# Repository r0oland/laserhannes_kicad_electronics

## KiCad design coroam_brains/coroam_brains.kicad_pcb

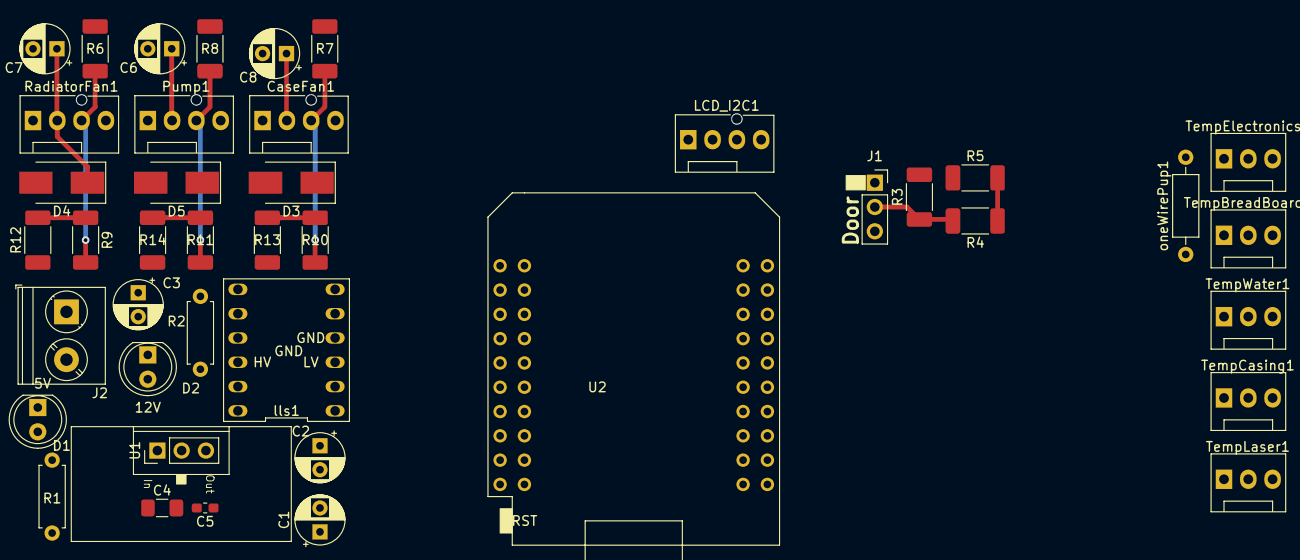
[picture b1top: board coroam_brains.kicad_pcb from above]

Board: 2 copper layers, 42 parts (0 on the bottom side), 23 nets.

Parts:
C1, C2, C3, C6, C7, C8: 22u; CP_Radial_D5.0mm_P2.50mm
C4: 0.33u; C_1206_3216Metric_Pad1.42x1.75mm_HandSolder
C5: 0.1u; C_0603_1608Metric_Pad1.05x0.95mm_HandSolder
CaseFan1: Fan_4pin; FanPinHeader_1x04_P2.54mm_Vertical
D1: 5V; LED_D5.0mm
D2: 12V; LED_D5.0mm
D3, D4, D5: D_Small_ALT; D_SMB_Handsoldering
J1: OpenCirc; PinSocket_1x03_P2.54mm_Vertical
J2: 12V_in; TerminalBlock_Phoenix_PT-1,5-2-5.0-H_1x02_P5.00mm_Horizontal
LCD_I2C1: LCD_I2C; FanPinHeader_1x04_P2.54mm_Vertical
Pump1: Fan_4pin; FanPinHeader_1x04_P2.54mm_Vertical
R1: 150; R_Axial_DIN0207_L6.3mm_D2.5mm_P7.62mm_Horizontal
R2: 560; R_Axial_DIN0207_L6.3mm_D2.5mm_P7.62mm_Horizontal
R3, R5, R6, R7, R8, R12, R13, R14: 10k; R_2010_5025Metric_Pad1.52x2.65mm_HandSolder
R4, R9, R10, R11: 5.1k; R_2010_5025Metric_Pad1.52x2.65mm_HandSolder
RadiatorFan1: Fan_4pin; FanPinHeader_1x04_P2.54mm_Vertical
TempBreadBoard1: DigiTempSens1; FanPinHeader_1x03_P2.54mm_Vertical
TempCasing1: DigiTempSens1; FanPinHeader_1x03_P2.54mm_Vertical
TempElectronics1: DigiTempSens1; FanPinHeader_1x03_P2.54mm_Vertical
TempLaser1: DigiTempSens1; FanPinHeader_1x03_P2.54mm_Vertical
TempWater1: DigiTempSens1; FanPinHeader_1x03_P2.54mm_Vertical
U1: L7805; PinHeader_1x03_P2.54mm_Vertical
U2: mini_esp32
lls1: level_shifter; level_shifte
oneWirePup1: 4.7k; R_Axial_DIN0207_L6.3mm_D2.5mm_P10.16mm_Horizontal

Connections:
+3V3: C1.1, TempBreadBoard1.3, TempCasing1.3, TempElectronics1.3, TempLaser1.3, TempWater1.3, U2.16, lls1.3, oneWirePup1.1
+5V: C2.1, C5.1, J1.3, R1.2, R6.1, R7.1, R8.1, U1.3, U2.35, lls1.10
+12V: C3.1, C4.1, C6.1, C7.1, C8.1, CaseFan1.2, D3.1, D4.1, D5.1, J2.1, Pump1.2, R2.2, RadiatorFan1.2, U1.1
CaseFanPWM: CaseFan1.4, lls1.8
CaseFanPWM_3V: U2.8, lls1.5
CaseFanTach: CaseFan1.3, R7.2, R10.2
CaseFanTach_3V: R10.1, R13.2, U2.7
Door_3V: R4.1, R5.2, U2.26
Door_5V: J1.2, R3.1, R4.2
GND: C1.2, C2.2, C3.2, C4.2, C5.2, C6.2, C7.2, C8.2, CaseFan1.1, D1.1, D2.1, D3.2, D4.2, D5.2, J1.1, J2.2, LCD_I2C1.1, Pump1.1, R3.2, R5.1, R12.1, R13.1, R14.1, RadiatorFan1.1, TempBreadBoard1.1, TempCasing1.1, TempLaser1.1, TempWater1.1, U1.2, U2.1, U2.22, U2.33, lls1.4, lls1.9
unnamed: D1.2, R1.1
unnamed: D2.2, R2.1
OneWireBus: TempBreadBoard1.2, TempCasing1.2, TempElectronics1.2, TempLaser1.2, TempWater1.2, U2.12, oneWirePup1.2
PumpPWM: Pump1.4, lls1.11
PumpPWM_3V: U2.6, lls1.2
PumpTach: Pump1.3, R8.2, R11.2
PumpTach_3V: R11.1, R14.2, U2.5
RadFanPWM: RadiatorFan1.4, lls1.7
RadFanPWM_3V: U2.10, lls1.6
RadFanTach: R6.2, R9.2, RadiatorFan1.3
RadFanTach_3V: R9.1, R12.2, U2.9
SCL: LCD_I2C1.3, U2.25
SDA: LCD_I2C1.2, U2.27

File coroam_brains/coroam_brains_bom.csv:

"Id";"Designator";"Package";"Quantity";"Designation";"Supplier and ref";
1;"C1,C2,C3,C6,C7,C8";"CP_Radial_D5.0mm_P2.50mm";6;"22u";;;
2;"C4";"CP_Radial_D5.0mm_P2.50mm";1;"0.33u";;;
3;"C5";"CP_Radial_D5.0mm_P2.50mm";1;"0.1u";;;
4;"D1";"LED_D5.0mm";1;"Red";;;
5;"D2";"LED_D5.0mm";1;"Green";;;
6;"LCD_I2C1";"FanPinHeader_1x04_P2.54mm_Vertical";1;"LCD_I2C";;;
7;"lls1";"level_shifte";1;"level_shifter";;;
8;"oneWirePup1";"R_Axial_DIN0207_L6.3mm_D2.5mm_P10.16mm_Horizontal";1;"4.7k";;;
9;"R1";"R_Axial_DIN0414_L11.9mm_D4.5mm_P15.24mm_Horizontal";1;"150";;;
10;"R2";"R_Axial_DIN0414_L11.9mm_D4.5mm_P15.24mm_Horizontal";1;"560";;;
11;"TempBreadBoard1,TempCasing1,TempElectronics1,TempLaser1,TempWater1";"FanPinHeader_1x03_P2.54mm_Vertical";5;"DigiTempSens1";;;
12;"U1";"PinHeader_1x03_P2.54mm_Vertical";1;"L7805";;;
13;"U2";"mini_esp32";1;"mini_esp32";;;
14;"CaseFan1,Pump1,RadiatorFan1";"FanPinHeader_1x04_P2.54mm_Vertical";3;"Fan_4pin";;;
15;"D3,D4,D5";"D_SMB_Handsoldering";3;"D_Small_ALT";;;
16;"J1";"PinSocket_1x03_P2.54mm_Vertical";1;"OpenCirc";;;
17;"R3,R5,R6,R7,R8,R12,R13,R14";"R_2010_5025Metric_Pad1.52x2.65mm_HandSolder";8;"10k";;;
18;"R4,R9,R10,R11";"R_2010_5025Metric_Pad1.52x2.65mm_HandSolder";4;"5.1k";;;
19;"R9";"R_2010_5025Metric_Pad1.52x2.65mm_HandSolder";1;"5.1";;;

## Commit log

2020-09-05 moving kicad projects into their own repo
2020-09-11 weird submodule popping up...
2020-09-11 trying schematic on new pc
2020-09-12 minor brain sch changes
2020-09-15 finishing brains schematics
2020-09-15 minor bug fix on coroam brain
2020-09-16 fixing few more bugs
2020-09-17 brains schematic debugged, now for the design
